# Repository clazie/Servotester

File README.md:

# Servotester

Arduino compatible Servo Tester with 16x2 display. Layout and firmware.

)

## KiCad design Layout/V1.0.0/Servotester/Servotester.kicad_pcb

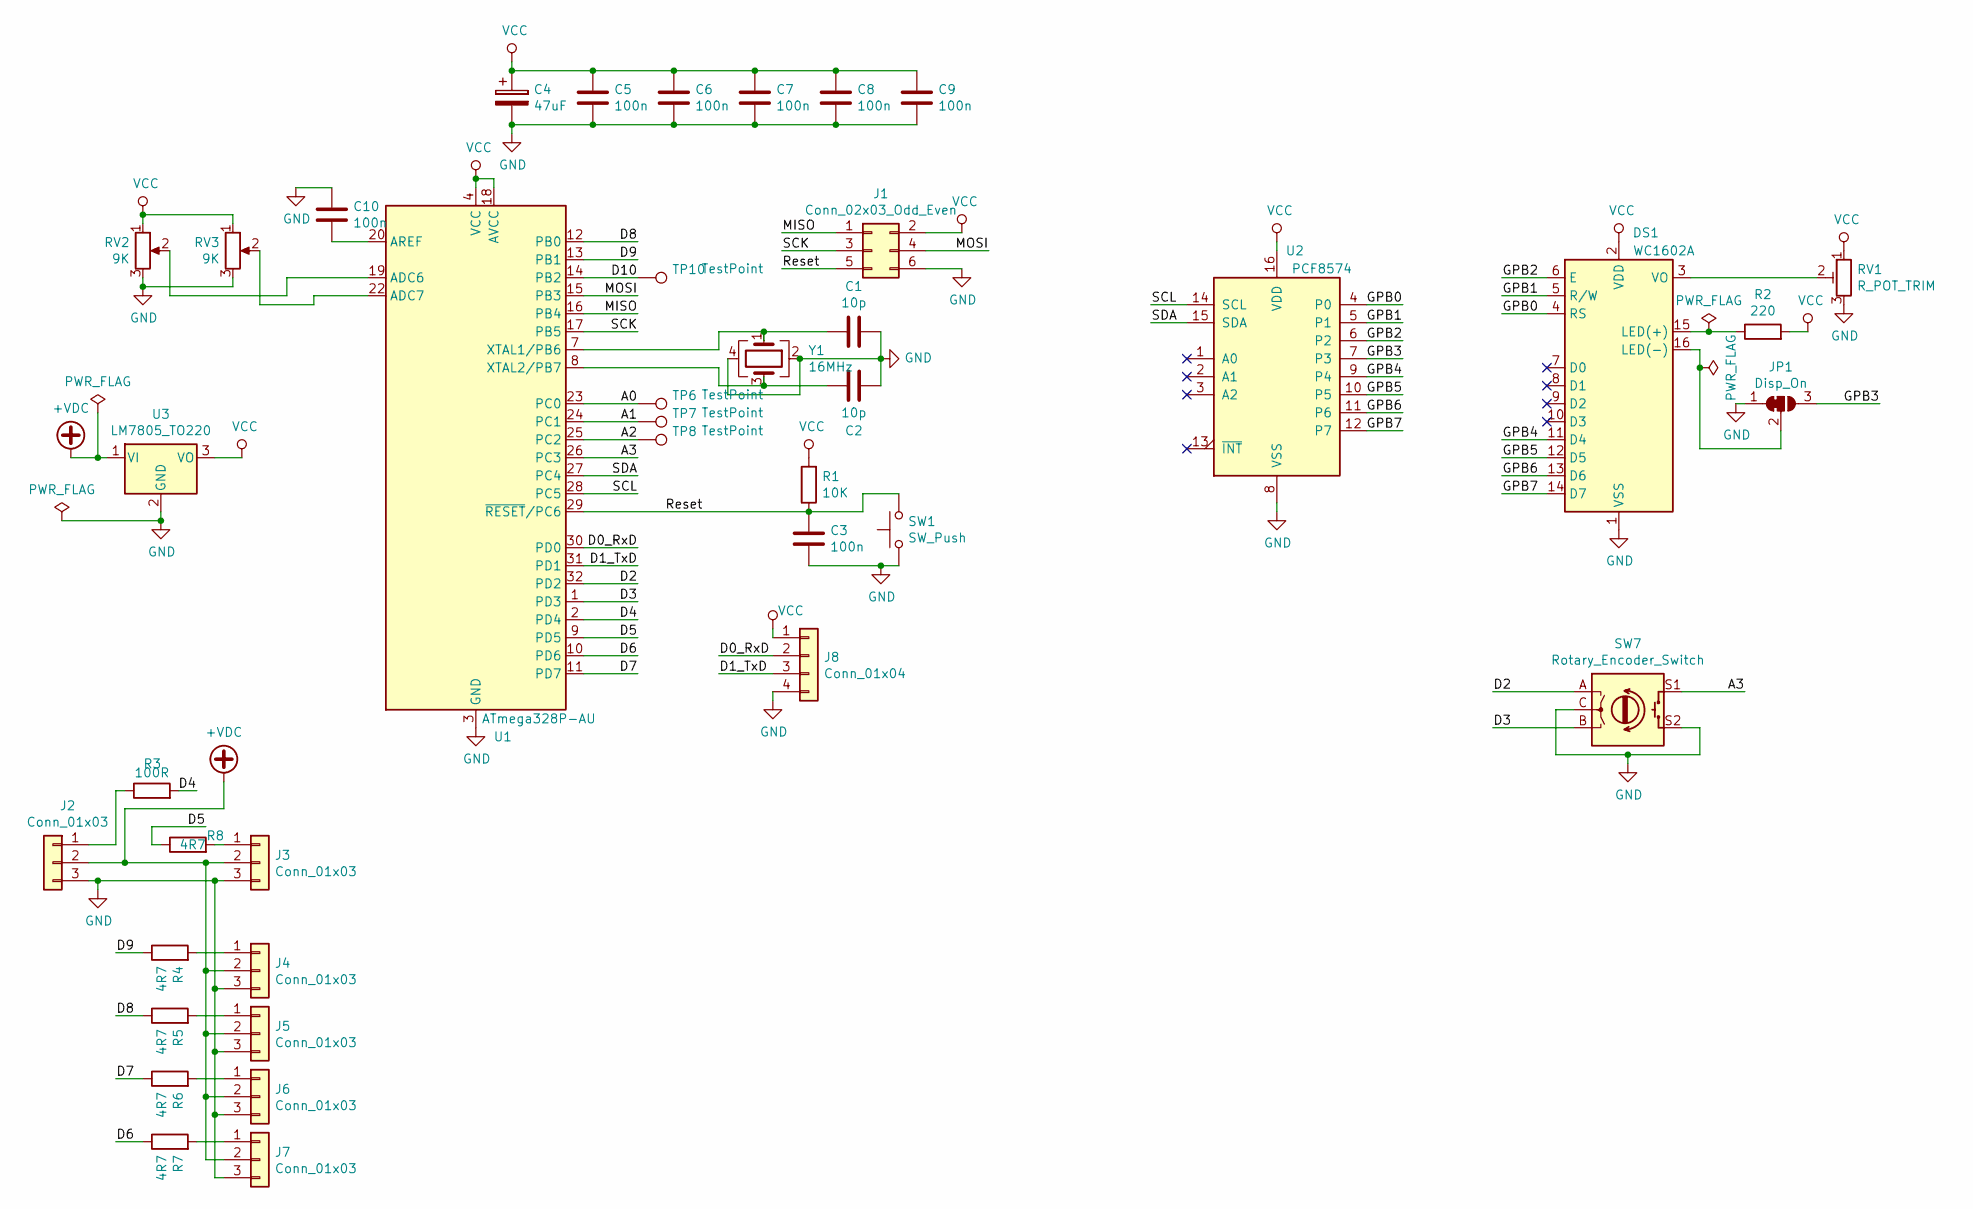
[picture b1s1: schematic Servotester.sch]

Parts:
C1, C2: 10p; C_0603_1608Metric
C3, C5, C6, C7, C8, C9, C10: 100n; C_0603_1608Metric
C4: 47uF; CP_Elec_5x4.5
DS1: WC1602A
J1: Conn_02x03_Odd_Even; PinHeader_2x03_P2.54mm_Vertical
J2, J3, J4, J5, J6, J7: Conn_01x03; PinHeader_1x03_P2.54mm_Horizontal
J8: Conn_01x04; PinHeader_1x04_P2.54mm_Vertical
JP1: Disp_On; SolderJumper-3_P1.3mm_Bridged12_Pad1.0x1.5mm_NumberLabels
R1: 10K; R_0603_1608Metric
R2: 220; R_0603_1608Metric
R3: 100R; R_0603_1608Metric
R4, R5, R6, R7, R8: 4R7; R_0603_1608Metric
RV1: R_POT_TRIM; Potentiometer_Bourns_TC33X_Vertical
RV2, RV3: 9K; Potentiometer_Alps_RK09K_Single_Vertical
SW1: SW_Push; SW_SPST_B3U-1000P
SW7: Rotary_Encoder_Switch; RotaryEncoder_Alps_EC11E-Switch_Vertical_H20mm
TP6, TP7, TP8, TP10: TestPoint; TestPoint_Pad_D1.5mm
U1: ATmega328P-AU; TQFP-32_7x7mm_P0.8mm
U2: PCF8574; SOIC-16_4.55x10.3mm_P1.27mm
U3: LM7805_TO220; TO-220-3_Vertical
Y1: 16MHz; Crystal_SMD_3225-4Pin_3.2x2.5mm_HandSoldering

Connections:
+VDC: J2.2, J3.2, J4.2, J5.2, J6.2, J7.2, U3.1 (VI)
/A0: TP6.1, U1.23 (PC0)
/A1: TP7.1, U1.24 (PC1)
/A2: TP8.1, U1.25 (PC2)
/A3: SW7.S1, U1.26 (PC3)
/D0_RxD: J8.2, U1.30 (PD0)
/D1_TxD: J8.3, U1.31 (PD1)
/D2: SW7.A, U1.32 (PD2)
/D3: SW7.B, U1.1 (PD3)
/D4: R3.2, U1.2 (PD4)
/D5: R8.1, U1.9 (PD5)
/D6: R7.1, U1.10 (PD6)
/D7: R6.1, U1.11 (PD7)
/D8: R5.1, U1.12 (PB0)
/D9: R4.1, U1.13 (PB1)
/D10: TP10.1, U1.14 (PB2)
/GPB0: DS1.4 (RS), U2.4 (P0)
/GPB1: DS1.5 (R/W), U2.5 (P1)
/GPB2: DS1.6 (E), U2.6 (P2)
/GPB3: JP1.3 (B), U2.7 (P3)
/GPB4: DS1.11 (D4), U2.9 (P4)
/GPB5: DS1.12 (D5), U2.10 (P5)
/GPB6: DS1.13 (D6), U2.11 (P6)
/GPB7: DS1.14 (D7), U2.12 (P7)
/MISO: J1.1, U1.16 (PB4)
/MOSI: J1.4, U1.15 (PB3)
/Reset: C3.2, J1.5, R1.1, SW1.2, U1.29 (~RESET~/PC6)
/SCK: J1.3, U1.17 (PB5)
/SCL: U1.28 (PC5), U2.14 (SCL)
/SDA: U1.27 (PC4), U2.15 (SDA)
GND: C1.1, C2.1, C3.1, C4.2, C5.1, C6.1, C7.1, C8.1, C9.1, C10.2, DS1.1 (VSS), J1.6, J2.3, J3.3, J4.3, J5.3, J6.3, J7.3, J8.4, JP1.1 (A), RV1.3, RV2.3, RV3.3, SW1.1, SW7.C, SW7.S2, U1.3 (GND), U1.5 (GND), U1.21 (GND), U2.8 (VSS), U3.2 (GND), Y1.2, Y1.4
unnamed: C1.2, U1.7 (XTAL1/PB6), Y1.1
unnamed: C2.2, U1.8 (XTAL2/PB7), Y1.3
unnamed: C10.1, U1.20 (AREF)
unnamed: DS1.3 (VO), RV1.2
unnamed: DS1.15 (LED(+)), R2.1
unnamed: DS1.16 (LED(-)), JP1.2 (C)
unnamed: J2.1, R3.1
unnamed: J3.1, R8.2
unnamed: J4.1, R4.2
unnamed: J5.1, R5.2
unnamed: J6.1, R6.2
unnamed: J7.1, R7.2
unnamed: RV2.2, U1.19 (ADC6)
unnamed: RV3.2, U1.22 (ADC7)
VCC: C4.1, C5.2, C6.2, C7.2, C8.2, C9.2, DS1.2 (VDD), J1.2, J8.1, R1.2, R2.2, RV1.1, RV2.1, RV3.1, U1.4 (VCC), U1.6 (VCC), U1.18 (AVCC), U2.16 (VDD), U3.3 (VO)

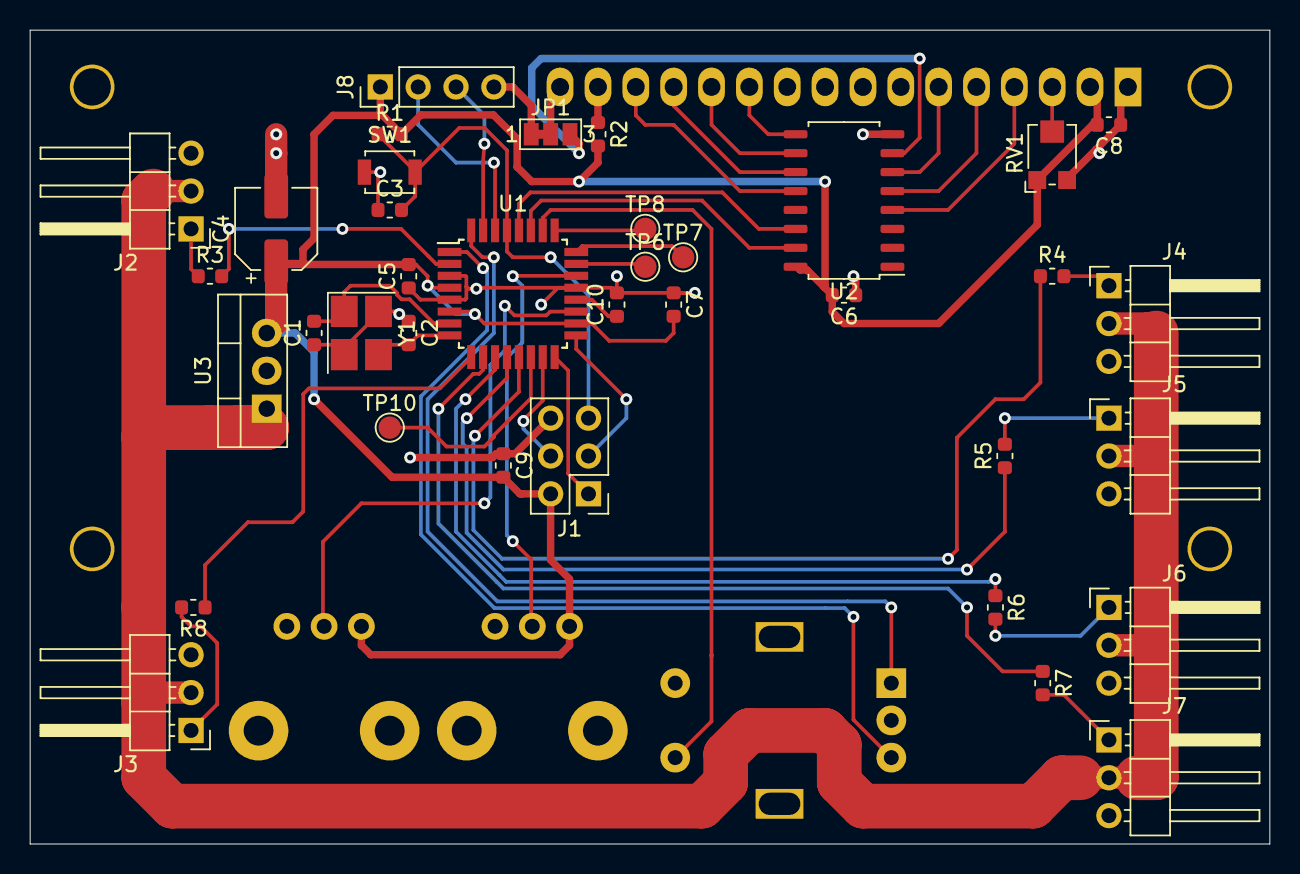
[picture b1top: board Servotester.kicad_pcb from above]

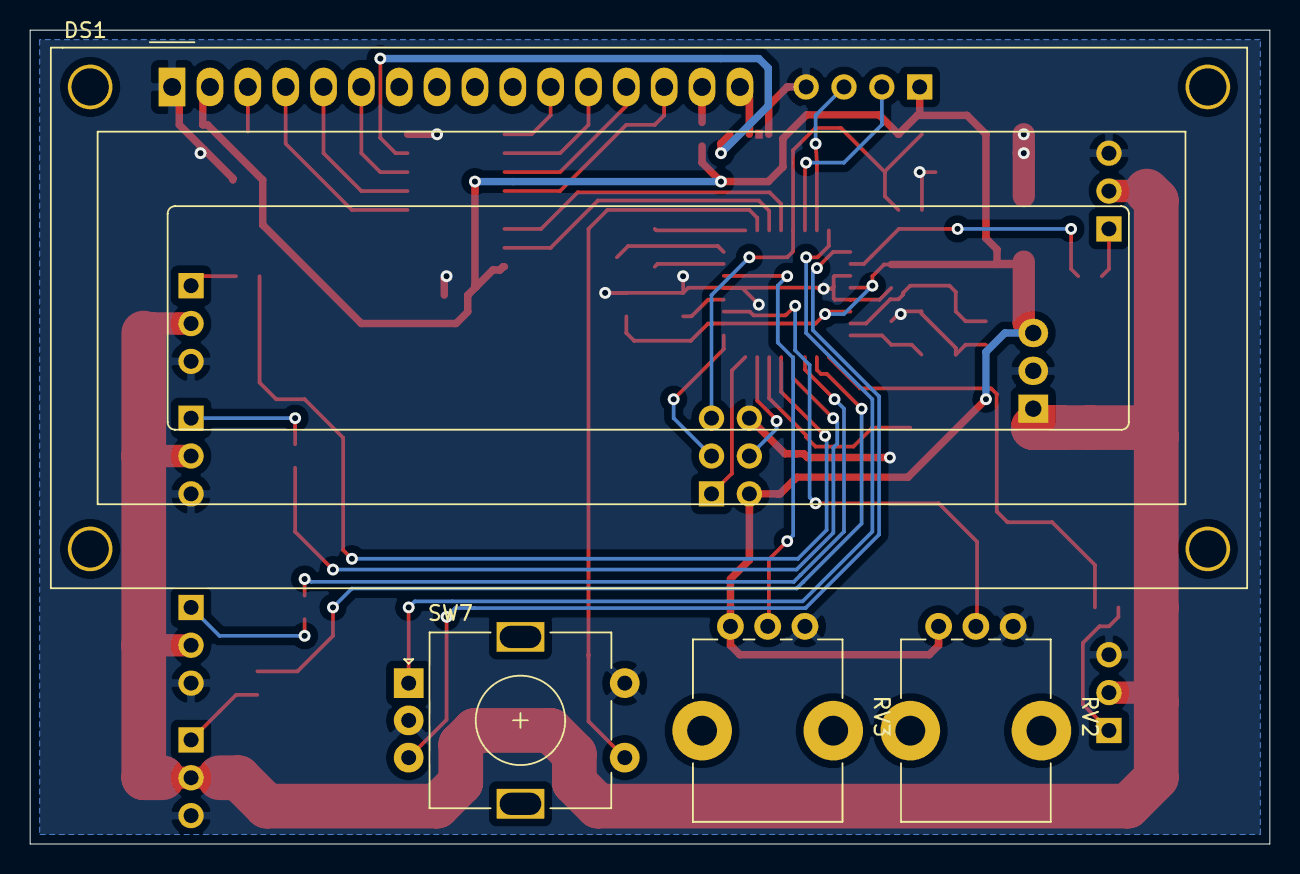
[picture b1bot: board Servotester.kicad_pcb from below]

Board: 2 copper layers, 83.2 x 54.6 mm, 41 parts (4 on the bottom side), 46 nets.

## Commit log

2021-10-01 Github initial checkin
2021-10-01 Readme corrected
2021-10-01 4 Outputs and function neutal
2021-10-04 Menu change and Encoder acceleration.
2021-10-06 Test for timed display refesh
2021-10-07 First functional version with Servo timer
